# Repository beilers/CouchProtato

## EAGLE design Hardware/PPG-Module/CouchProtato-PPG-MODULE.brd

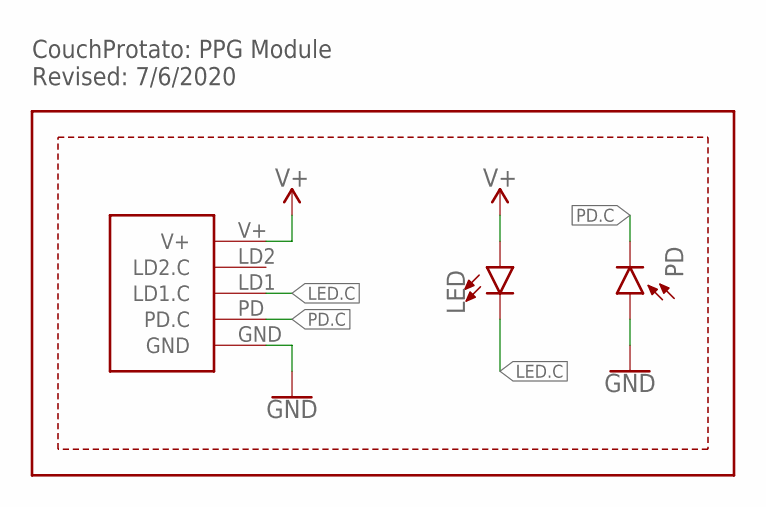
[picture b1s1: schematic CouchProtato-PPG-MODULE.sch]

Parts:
LED: LED0805; LED-0805
PD: PHOTODIODE2-SMD.GULLWING; 2-SMD.GULLWING
U$3: PPG.MODULE.2

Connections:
GND: PD.+ (A), U$3.GND
LED.C: LED.C, U$3.LD1 (LD1.C)
PD.C: PD.- (C), U$3.PD (PD.C)
V+: LED.A, U$3.V+

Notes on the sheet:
CouchProtato: PPG Module Revised: 7/6/2020

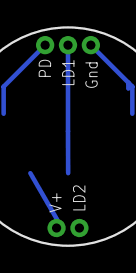
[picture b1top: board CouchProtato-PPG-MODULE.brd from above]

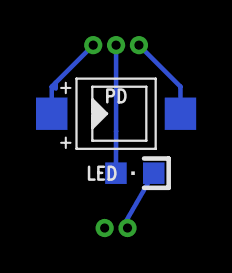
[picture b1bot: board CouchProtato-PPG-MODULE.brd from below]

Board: 2 copper layers, 3 parts (2 on the bottom side), 4 nets.

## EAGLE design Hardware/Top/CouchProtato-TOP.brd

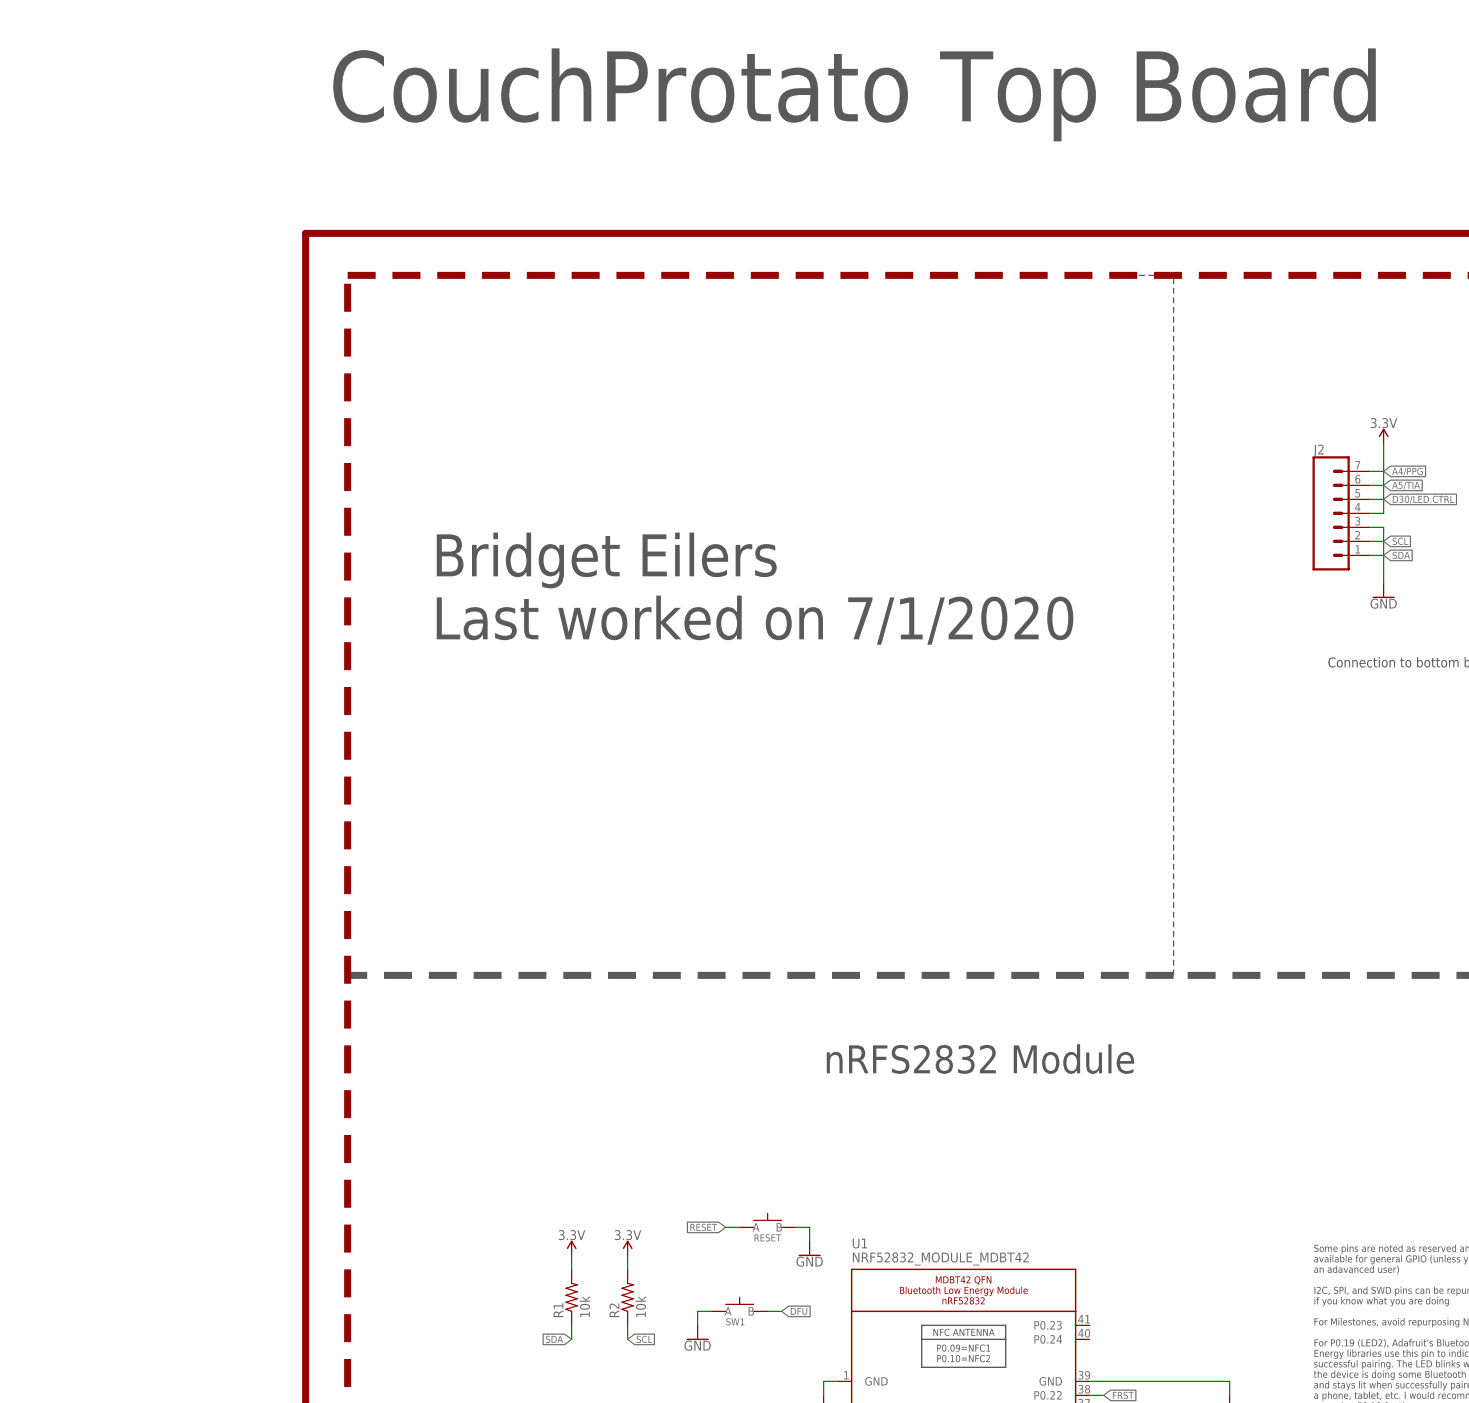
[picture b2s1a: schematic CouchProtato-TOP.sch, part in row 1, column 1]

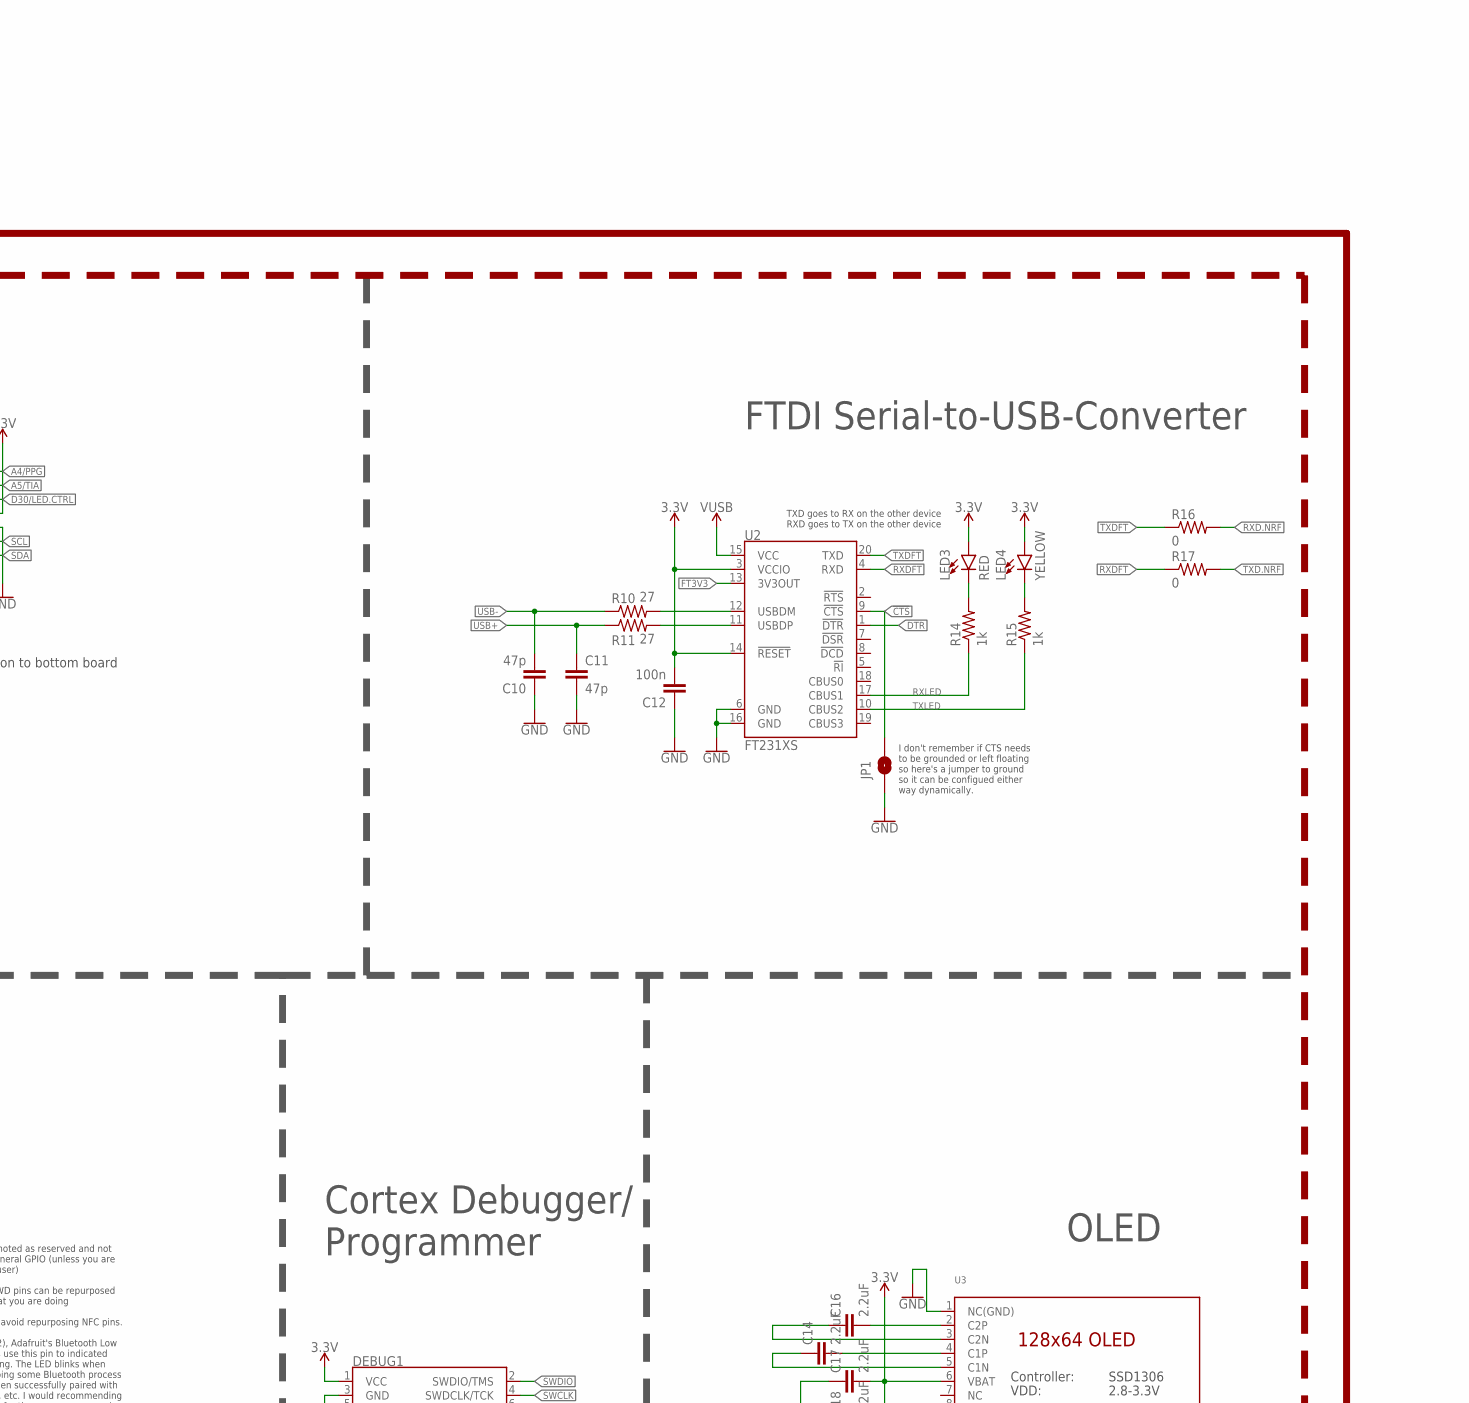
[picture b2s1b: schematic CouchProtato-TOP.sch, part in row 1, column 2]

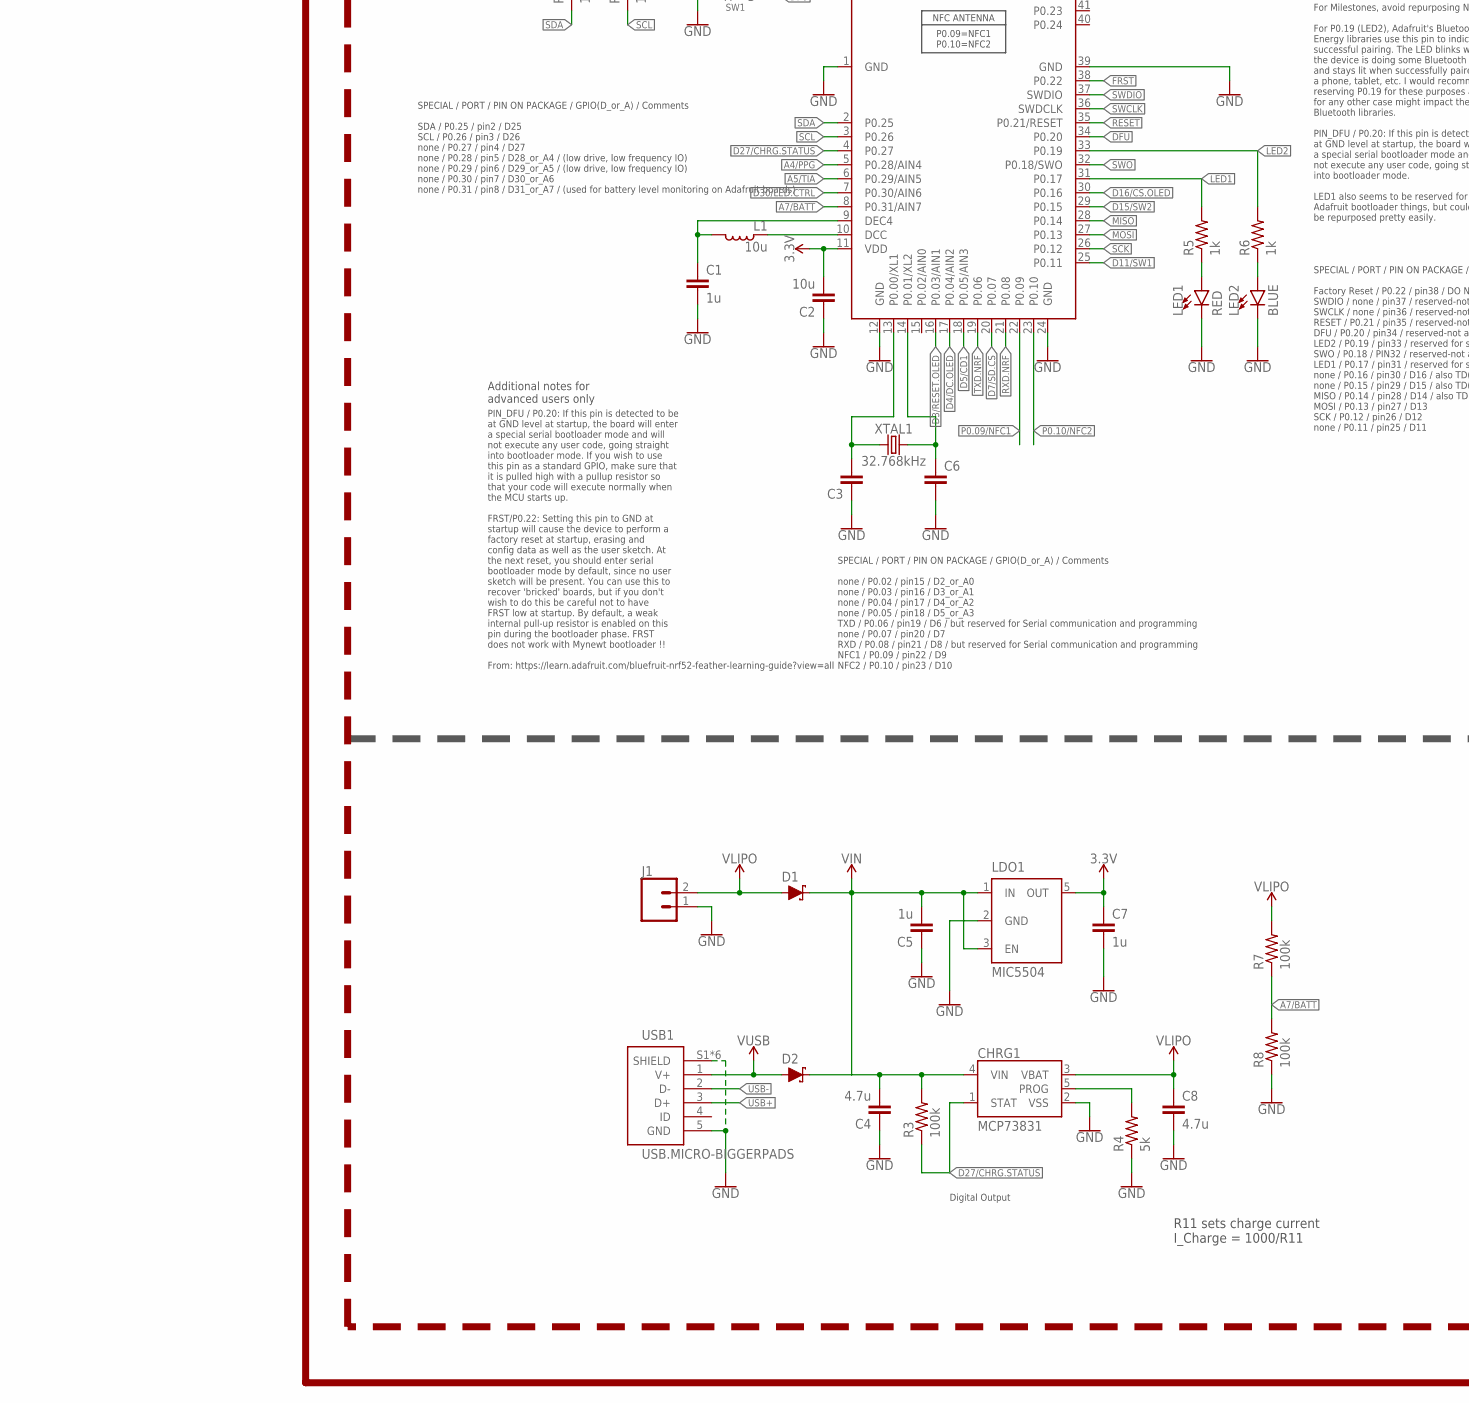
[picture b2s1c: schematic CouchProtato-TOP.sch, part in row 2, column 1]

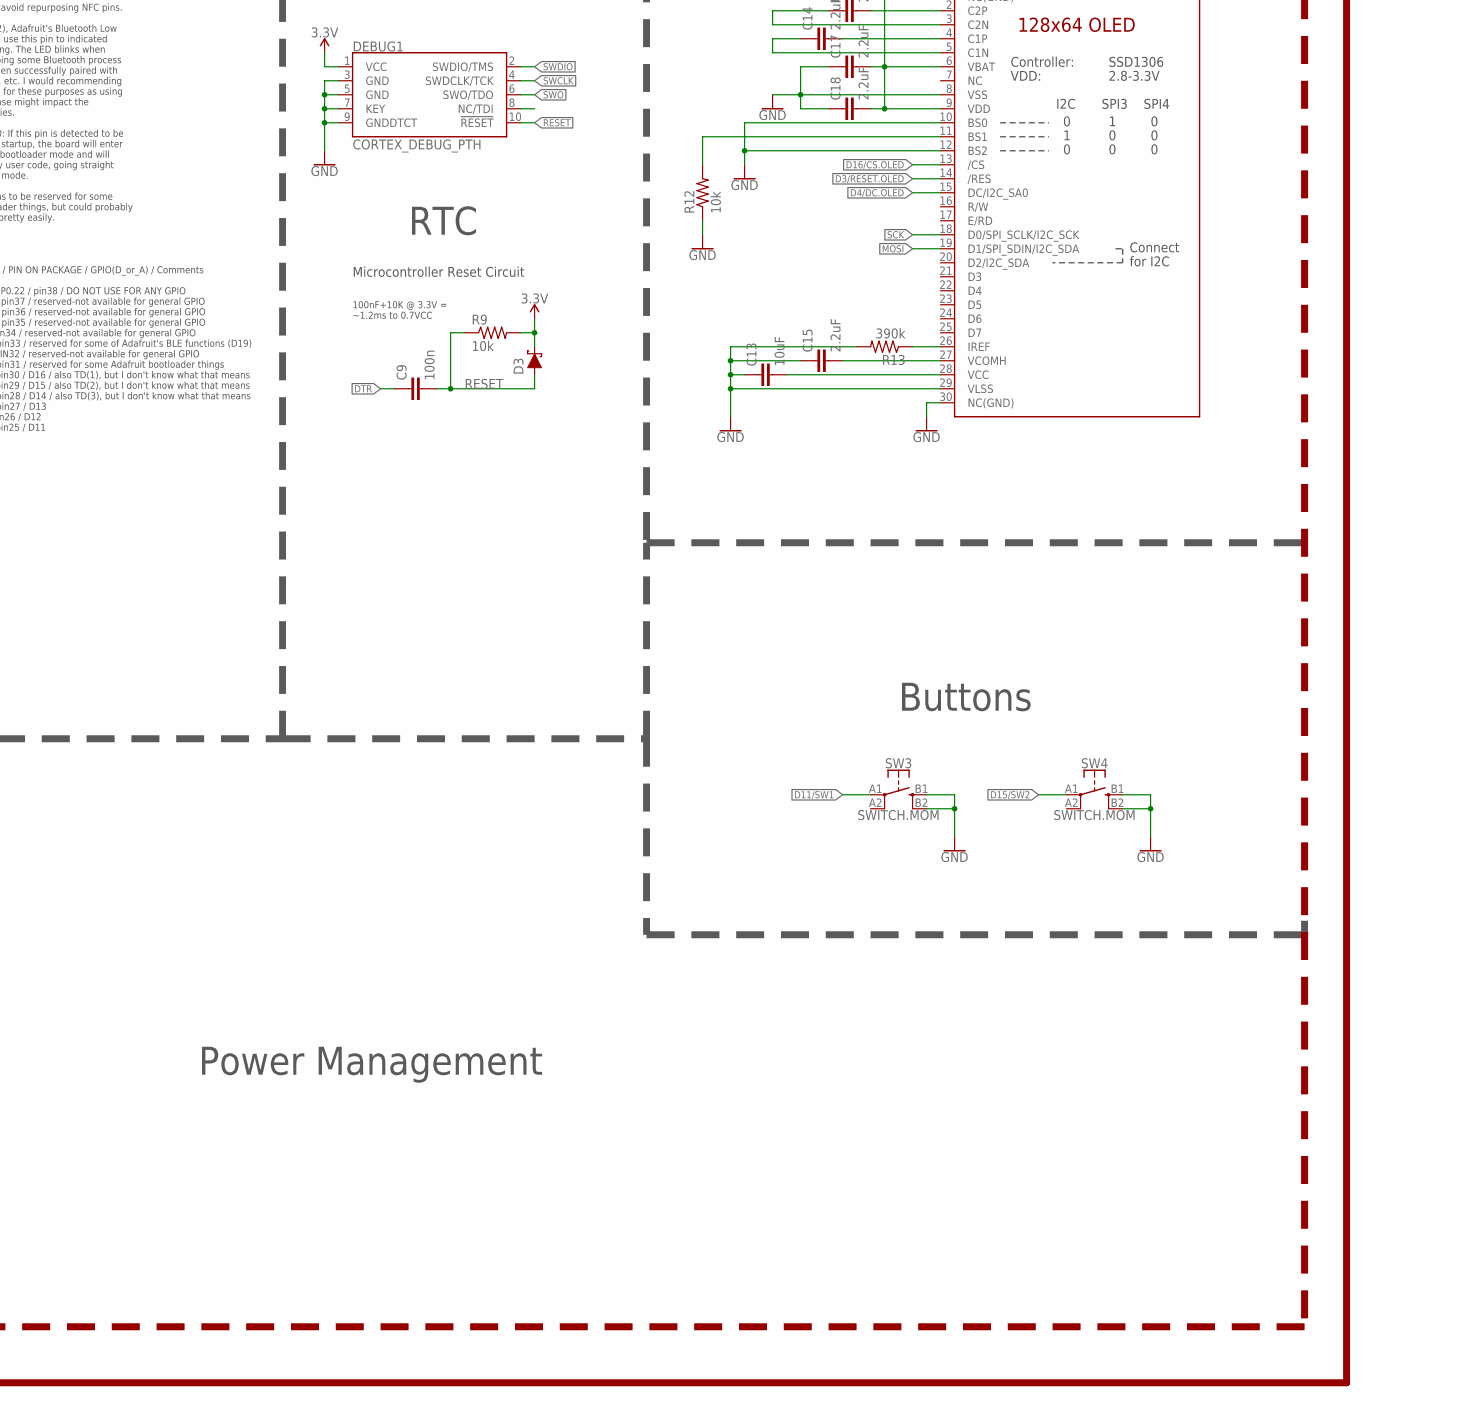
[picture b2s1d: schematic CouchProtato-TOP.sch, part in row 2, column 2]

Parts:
C1, C5, C7: 1u; C0603
C2: 10u; C0805
C3, C6: CAPACITOR0603; C0603
C4, C8: 4.7u; C0603
C9, C12: 100n; C0603
C10, C11: 47p; C0603
C13: 10uF; C0603
C14, C16, C17, C18: 2.2uF; C0402
C15: 2.2uF; C0603
CHRG1: MCP73831; SOT23-5
D1, D2, D3: SCHOTTKY-USC; USC
DEBUG1: CORTEX_DEBUG_PTH; 2X5-PTH-1.27MM
J1: CONN_02; 1X02
J2: CONN_07-1.27MM; 1X07_1.27MM
JP1: JUMPER-SMT_2_NO_SILK; SMT-JUMPER_2_NO_SILK
L1: 10u; L0603
LDO1: MIC5504; SOT23-5
LED1, LED3: RED; LED-0603
LED2: BLUE; LED-0603
LED4: YELLOW; LED-0603
R1, R2, R9, R12: 10k; R0603
R3, R7, R8: 100k; R0603
R4: 5k; R0603
R5, R6, R14, R15: 1k; R0603
R10, R11: 27; R0603
R13: 390k; R0603
R16, R17: 0; R0603
RESET: SPST-PTS830GG140-COPY.1-3; BUTTON-GULLWING
SW1: SPST-PTS830GG140-COPY.1-3; BUTTON-GULLWING
SW3, SW4: SWITCH.MOM; TACTILE_SWITCH_SMD_6.2MM_TALL
U1: NRF52832_MODULE_MDBT42; BLE_MODULE_RAYTAC_MDBT42
U2: FT231XS; SSOP20_L
U3: DISP_OLED_UG-2864HSWEG01-NO-WRAPAROUND; UG-2864HSWEG01_0.96IN_NO-WRAPAROUND
USB1: USB.MICRO-BIGGERPADS; USB-MICRO-01.BIGGERPADS
XTAL1: 32.768kHz; 2-SMD.NOLEAD.2.0MMTO1.2MM

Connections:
3.3V: C2.2, C7.1, C12.2, C17.2, C18.2, D3.- (C), DEBUG1.1 (VCC), J2.4, LDO1.5 (OUT), LED3.A, LED4.A, R1.2, R2.2, R9.2, U1.11 (VDD), U2.3 (VCCIO), U2.14 (!RESET), U3.6 (VBAT), U3.9 (VDD)
!CTS: JP1.2, U2.9 (!CTS)
A4/PPG: J2.7, U1.5 (P0.28/AIN4)
A5/TIA: J2.6, U1.6 (P0.29/AIN5)
A7/BATT: R7.1, R8.2, U1.8 (P0.31/AIN7)
D3/RESET.OLED: U1.16 (P0.03/AIN1), U3.14 (/RES)
D4/DC.OLED: U1.17 (P0.04/AIN2), U3.15 (DC/I2C_SA0)
D5/CD1: U1.18 (P0.05/AIN3)
D7/SD.CS: U1.20 (P0.07)
D11/SW1: SW3.A1 (1), U1.25 (P0.11)
D15/SW2: SW4.A1 (1), U1.29 (P0.15)
D16/CS.OLED: U1.30 (P0.16), U3.13 (/CS)
D27/CHRG.STATUS: CHRG1.1 (STAT), R3.1, U1.4 (P0.27)
D30/LED.CTRL: J2.5, U1.7 (P0.30/AIN6)
DFU: SW1.3 (B), U1.34 (P0.20)
DTR: C9.1, U2.1 (!DTR)
FRST: U1.38 (P0.22)
FT3V3: U2.13 (3V3OUT)
GND: C1.2, C2.1, C3.1, C4.1, C5.1, C6.2, C7.2, C8.2, C10.1, C11.2, C12.1, C13.1, C15.1, C17.1, C18.1, CHRG1.2 (VSS), DEBUG1.3 (GND), DEBUG1.5 (GND), DEBUG1.7 (KEY), DEBUG1.9 (GNDDTCT), J1.1, J2.3, JP1.1, LDO1.2 (GND), LED1.C, LED2.C, R4.1, R8.1, R12.1, R13.2, RESET.3 (B), SW1.1 (A), SW3.B1 (3), SW3.B2 (4), SW4.B1 (3), SW4.B2 (4), U1.1 (GND), U1.12 (GND), U1.24 (GND), U1.39 (GND), U2.6 (GND), U2.16 (GND), U3.1 (NC(GND)), U3.8 (VSS), U3.10 (BS0), U3.12 (BS2), U3.29 (VLSS), U3.30 (NC(GND)), USB1.5 (GND), USB1.S1 (SHIELD), USB1.S2 (SHIELD), USB1.S3 (SHIELD), USB1.S4 (SHIELD), USB1.S5 (SHIELD), USB1.S6 (SHIELD)
LED1: R5.2, U1.31 (P0.17)
LED2: R6.2, U1.33 (P0.19)
MISO: U1.28 (P0.14)
MOSI: U1.27 (P0.13), U3.19 (D1/SPI_SDIN/I2C_SDA)
unnamed: R12.2, U3.11 (BS1)
unnamed: R13.1, U3.26 (IREF)
unnamed: C16.2, U3.2 (C2P)
unnamed: C3.2, U1.13 (P0.00/XL1), XTAL1.P$1 (1)
unnamed: C16.1, U3.3 (C2N)
unnamed: C6.1, U1.14 (P0.01/XL2), XTAL1.P$2 (2)
unnamed: C14.2, U3.4 (C1P)
unnamed: C14.1, U3.5 (C1N)
unnamed: LED1.A, R5.1
unnamed: LED2.A, R6.1
unnamed: L1.1, U1.10 (DCC)
unnamed: C1.1, L1.2, U1.9 (DEC4)
unnamed: C13.2, U3.28 (VCC)
unnamed: C15.2, U3.27 (VCOMH)
unnamed: CHRG1.5 (PROG), R4.2
unnamed: R10.2, U2.12 (USBDM)
unnamed: R11.2, U2.11 (USBDP)
unnamed: LED3.C, R14.2
unnamed: LED4.C, R15.2
P0.09/NFC1: U1.22 (P0.09)
P0.10/NFC2: U1.23 (P0.10)
RESET: C9.2, D3.+ (A), DEBUG1.10 (!RESET), R9.1, RESET.1 (A), U1.35 (P0.21/RESET)
RXD.NRF: R16.2, U1.21 (P0.08)
RXDFT: R17.1, U2.4 (RXD)
RXLED: R14.1, U2.17 (CBUS1)
SCK: U1.26 (P0.12), U3.18 (D0/SPI_SCLK/I2C_SCK)
SCL: J2.2, R2.1, U1.3 (P0.26)
SDA: J2.1, R1.1, U1.2 (P0.25)
SWCLK: DEBUG1.4 (SWDCLK/TCK), U1.36 (SWDCLK)
SWDIO: DEBUG1.2 (SWDIO/TMS), U1.37 (SWDIO)
SWO: DEBUG1.6 (SWO/TDO), U1.32 (P0.18/SWO)
TXD.NRF: R17.2, U1.19 (P0.06)
TXDFT: R16.1, U2.20 (TXD)
TXLED: R15.1, U2.10 (CBUS2)
USB+: C11.1, R11.1, USB1.3 (D+)
USB-: C10.2, R10.1, USB1.2 (D-)
VIN: C4.2, C5.2, CHRG1.4 (VIN), D1.- (C), D2.- (C), LDO1.1 (IN), LDO1.3 (EN), R3.2
VLIPO: C8.1, CHRG1.3 (VBAT), D1.+ (A), J1.2, R7.2
V_USB: D2.+ (A), U2.15 (VCC), USB1.1 (V+)

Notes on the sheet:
Microcontroller Reset Circuit
100nF+10K @ 3.3V = ~1.2ms to 0.7VCC
SPECIAL / PORT / PIN ON PACKAGE / GPIO(D_or_A) / Comments SDA / P0.25 / pin2 / D25 SCL / P0.26 / pin3 / D26 none / P0.27 / pin4 / D27 none / P0.28 / pin5 / D28_or_A4 / (low drive, low frequency IO) none / P0.29 / pin6 / D29_or_A5 / (low drive, low frequency IO) none / P0.30 / pin7 / D30_or_A6 none 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
SPECIAL / PORT / PIN ON PACKAGE / GPIO(D_or_A) / Comments none / P0.02 / pin15 / D2_or_A0 none / P0.03 / pin16 / D3_or_A1 none / P0.04 / pin17 / D4_or_A2 none / P0.05 / pin18 / D5_or_A3 TXD / P0.06 / pin19 / D6 / but reserved for Serial communication and programming none / P0.07 / pin20 / D7 RXD / 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
SPECIAL / PORT / PIN ON PACKAGE / GPIO(D_or_A) / Comments Factory Reset / P0.22 / pin38 / DO NOT USE FOR ANY GPIO SWDIO / none / pin37 / reserved-not available for general GPIO SWCLK / none / pin36 / reserved-not available for general GPIO RESET / P0.21 / pin35 / reserved-not available for general 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
Some pins are noted as reserved and not available for general GPIO (unless you are an adavanced user) I2C, SPI, and SWD pins can be repurposed if you know what you are doing For Milestones, avoid repurposing NFC pins. For P0.19 (LED2), Adafruit's Bluetooth Low Energy libraries use this pin to indic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
PIN_DFU / P0.20: If this pin is detected to be at GND level at startup, the board will enter a special serial bootloader mode and will not execute any user code, going straight into bootloader mode. If you wish to use this pin as a standard GPIO, make sure that it is pulled high with a pullup resis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
Additional notes for advanced users only
nRFS2832 Module
OLED
Power Management
Buttons
Cortex Debugger/ Programmer
RTC
TXD goes to RX on the other device RXD goes to TX on the other device
I don't remember if CTS needs to be grounded or left floating so here's a jumper to ground so it can be configued either way dynamically.
FTDI Serial-to-USB-Converter
CouchProtato Top Board
Bridget Eilers Last worked on 7/1/2020
Connection to bottom board
Digital Output
R11 sets charge current I_Charge = 1000/R11

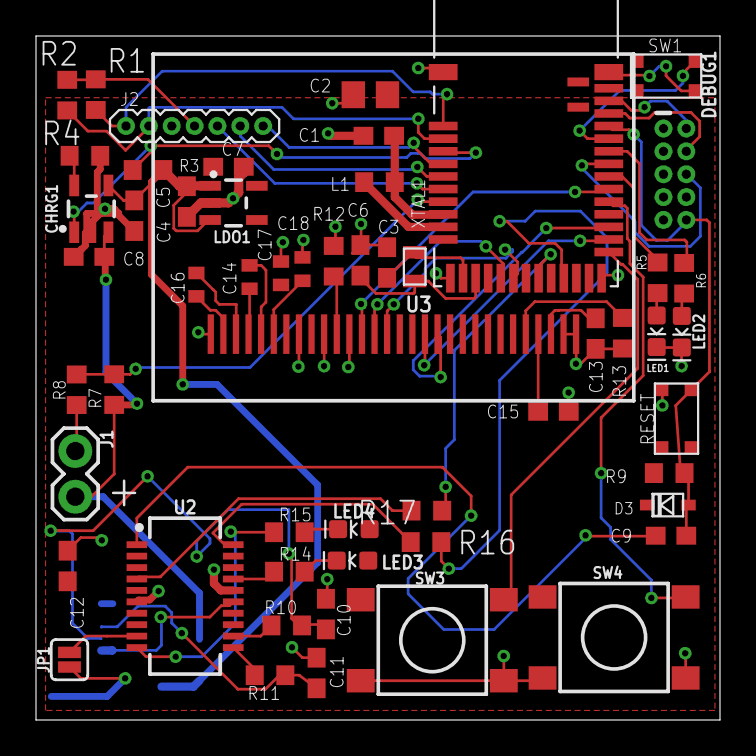
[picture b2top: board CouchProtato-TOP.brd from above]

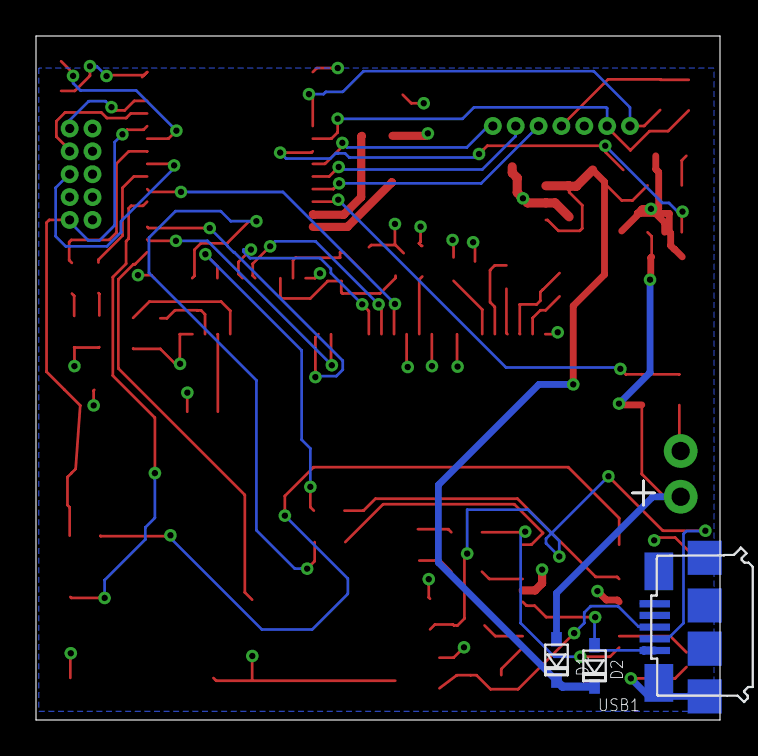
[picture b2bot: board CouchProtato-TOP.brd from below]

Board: 2 copper layers, 38.0 x 38.0 mm, 58 parts (3 on the bottom side), 55 nets.

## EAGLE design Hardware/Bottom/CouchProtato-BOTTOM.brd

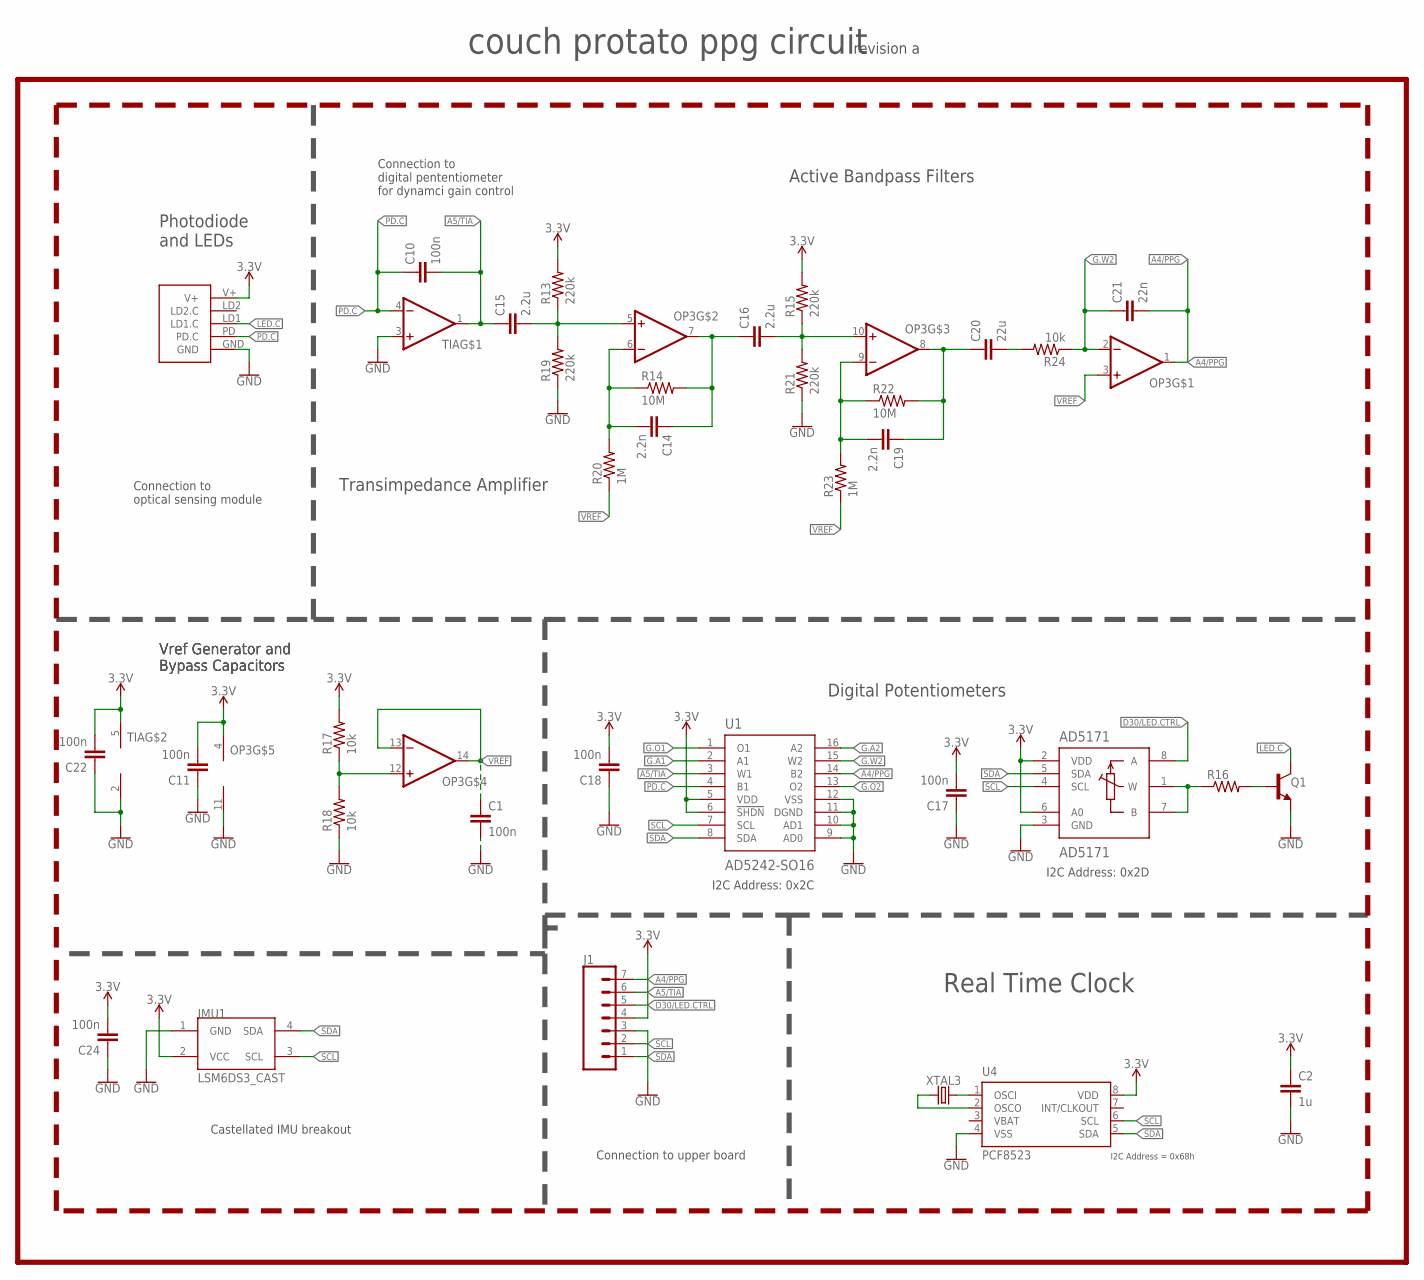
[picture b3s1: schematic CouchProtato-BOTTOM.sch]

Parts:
AD5171: AD5171; SOT-23-8
C1, C10, C11, C17, C18, C22, C24: 100n; C0603
C2: 1u; C0603
C14, C19: 2.2n; C0603
C15, C16: 2.2u; C0603
C20: 22u; C0603
C21: 22n; C0603
IMU1: LSM6DS3_CAST
J1: CONN_07-1.27MM; 1X07_1.27MM
OP3: OP-QUAD-SO14; SO14
Q1: NPN-GENERIC; SOT23-3
R13, R15, R19, R21: 220k; R0603
R14, R22: 10M; R0603
R16: RESISTOR0603; R0603
R17, R18: 10k; R0402
R20, R23: 1M; R0603
R24: 10k; R0603
TIA: OP-SINGLEOT; SOT23-5
U1: AD5242-SO16; SO16
U4: PCF8523; SO8; DIGIKEY 568-5306-1-ND
U$3: PPG.MODULE.2
XTAL3: 32.7680kHz; 2-SMD.NOLEAD.2.0MMTO1.2MM

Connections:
3.3V: AD5171.2 (VDD), AD5171.6 (A0), C2.1, C11.2, C17.2, C18.2, C22.2, C24.2, IMU1.2 (VCC), J1.4, OP3.4 (V+), R13.2, R15.2, R17.2, TIA.5 (V+), U1.5 (VDD), U1.6 (!SHDN), U4.8 (VDD), U$3.V+
A4/PPG: C21.2, J1.7, OP3.1 (OUT), U1.14 (B2)
A5/TIA: C10.2, C15.1, J1.6, TIA.1 (OUT), U1.3 (W1)
D30/LED.CTRL: AD5171.8 (A), J1.5
G.A1: U1.2 (A1)
G.A2: U1.16 (A2)
G.O1: U1.1 (O1)
G.O2: U1.13 (O2)
G.W2: C21.1, OP3.2 (-IN), R24.1, U1.15 (W2)
GND: AD5171.3 (GND), C1.2, C2.2, C11.1, C17.1, C18.1, C22.1, C24.1, IMU1.1 (GND), J1.3, OP3.11 (V-), Q1.2 (E), R18.1, R19.1, R21.1, TIA.2 (V-), TIA.3 (+IN), U1.9 (AD0), U1.10 (AD1), U1.11 (DGND), U1.12 (VSS), U4.4 (VSS), U$3.GND
LED.C: Q1.3 (C), U$3.LD1 (LD1.C)
unnamed: U4.2 (OSCO), XTAL3.P$1 (1)
unnamed: U4.1 (OSCI), XTAL3.P$2 (2)
unnamed: Q1.1 (B), R16.2
unnamed: AD5171.1 (W), AD5171.7 (B), R16.1
unnamed: OP3.12 (+IN), R17.1, R18.2
unnamed: C15.2, OP3.5 (+IN), R13.1, R19.2
unnamed: C14.2, OP3.6 (-IN), R14.1, R20.2
unnamed: C14.1, C16.1, OP3.7 (OUT), R14.2
unnamed: C16.2, OP3.10 (+IN), R15.1, R21.2
unnamed: C19.2, OP3.9 (-IN), R22.1, R23.2
unnamed: C19.1, C20.1, OP3.8 (OUT), R22.2
unnamed: C20.2, R24.2
PD.C: C10.1, TIA.4 (-IN), U1.4 (B1), U$3.PD (PD.C)
SCL: AD5171.4 (SCL), IMU1.3 (SCL), J1.2, U1.7 (SCL), U4.6 (SCL)
SDA: AD5171.5 (SDA), IMU1.4 (SDA), J1.1, U1.8 (SDA), U4.5 (SDA)
VBAT: U4.3 (VBAT)
VREF: C1.1, OP3.3 (+IN), OP3.13 (-IN), OP3.14 (OUT), R20.1, R23.1

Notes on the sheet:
Photodiode and LEDs
Active Bandpass Filters
Digital Potentiometers
Transimpedance Amplifier
I2C Address: 0x2C
I2C Address: 0x2D
Connection to optical sensing module
Connection to digital pententiometer for dynamci gain control
Connection to upper board
Castellated IMU breakout
Vref Generator and Bypass Capacitors
couch protato ppg circuit
revision a
I2C Address = 0x68h
Real Time Clock

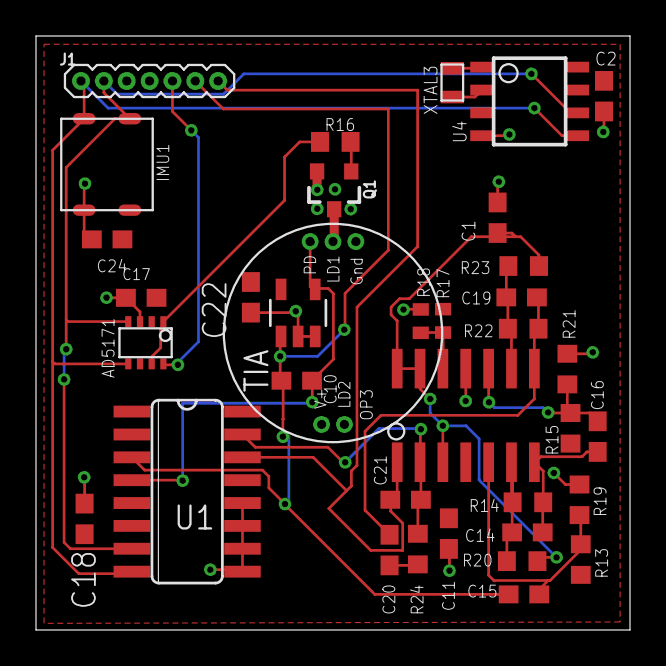
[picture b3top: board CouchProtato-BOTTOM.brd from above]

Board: 2 copper layers, 33.0 x 33.0 mm, 36 parts (0 on the bottom side), 23 nets.

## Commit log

2020-05-28 features list
2020-06-04 Adding all files to repo
2020-06-04 update files
2020-06-05 board update 6/4
2020-06-05 update schematic TOP 6/4
2020-06-11 Top schematic finished
2020-06-12 Finished routing top and bottom boards
2020-06-26 Power code set up
2020-06-27 Progress on routing bottom board and schematic
2020-06-28 finished routing bottom board and began top. finished take 003.
2020-06-28 In the middle of routing top board, working on OLED
2020-06-30 22.42 through take 3, continued routing top board
2020-07-01 Finished take 7, one more how to video to go, reorganizing and finalizing boards
2020-07-01 Finished first revisions of EAGLE designs for smartwatch
2020-07-02 deleted renumbering file, don't need
2020-07-06 added ppg module
2020-07-09 Added ppg board and schematic
2020-07-16 Added libraries to code
2020-07-23 Firmware updated. Can turn on LED with button using the push button library.
2020-08-04 Tested LCD Display on Arduino to resemble OLED
2020-08-13 Completed BOM's
2020-08-14 Edited BOM's
